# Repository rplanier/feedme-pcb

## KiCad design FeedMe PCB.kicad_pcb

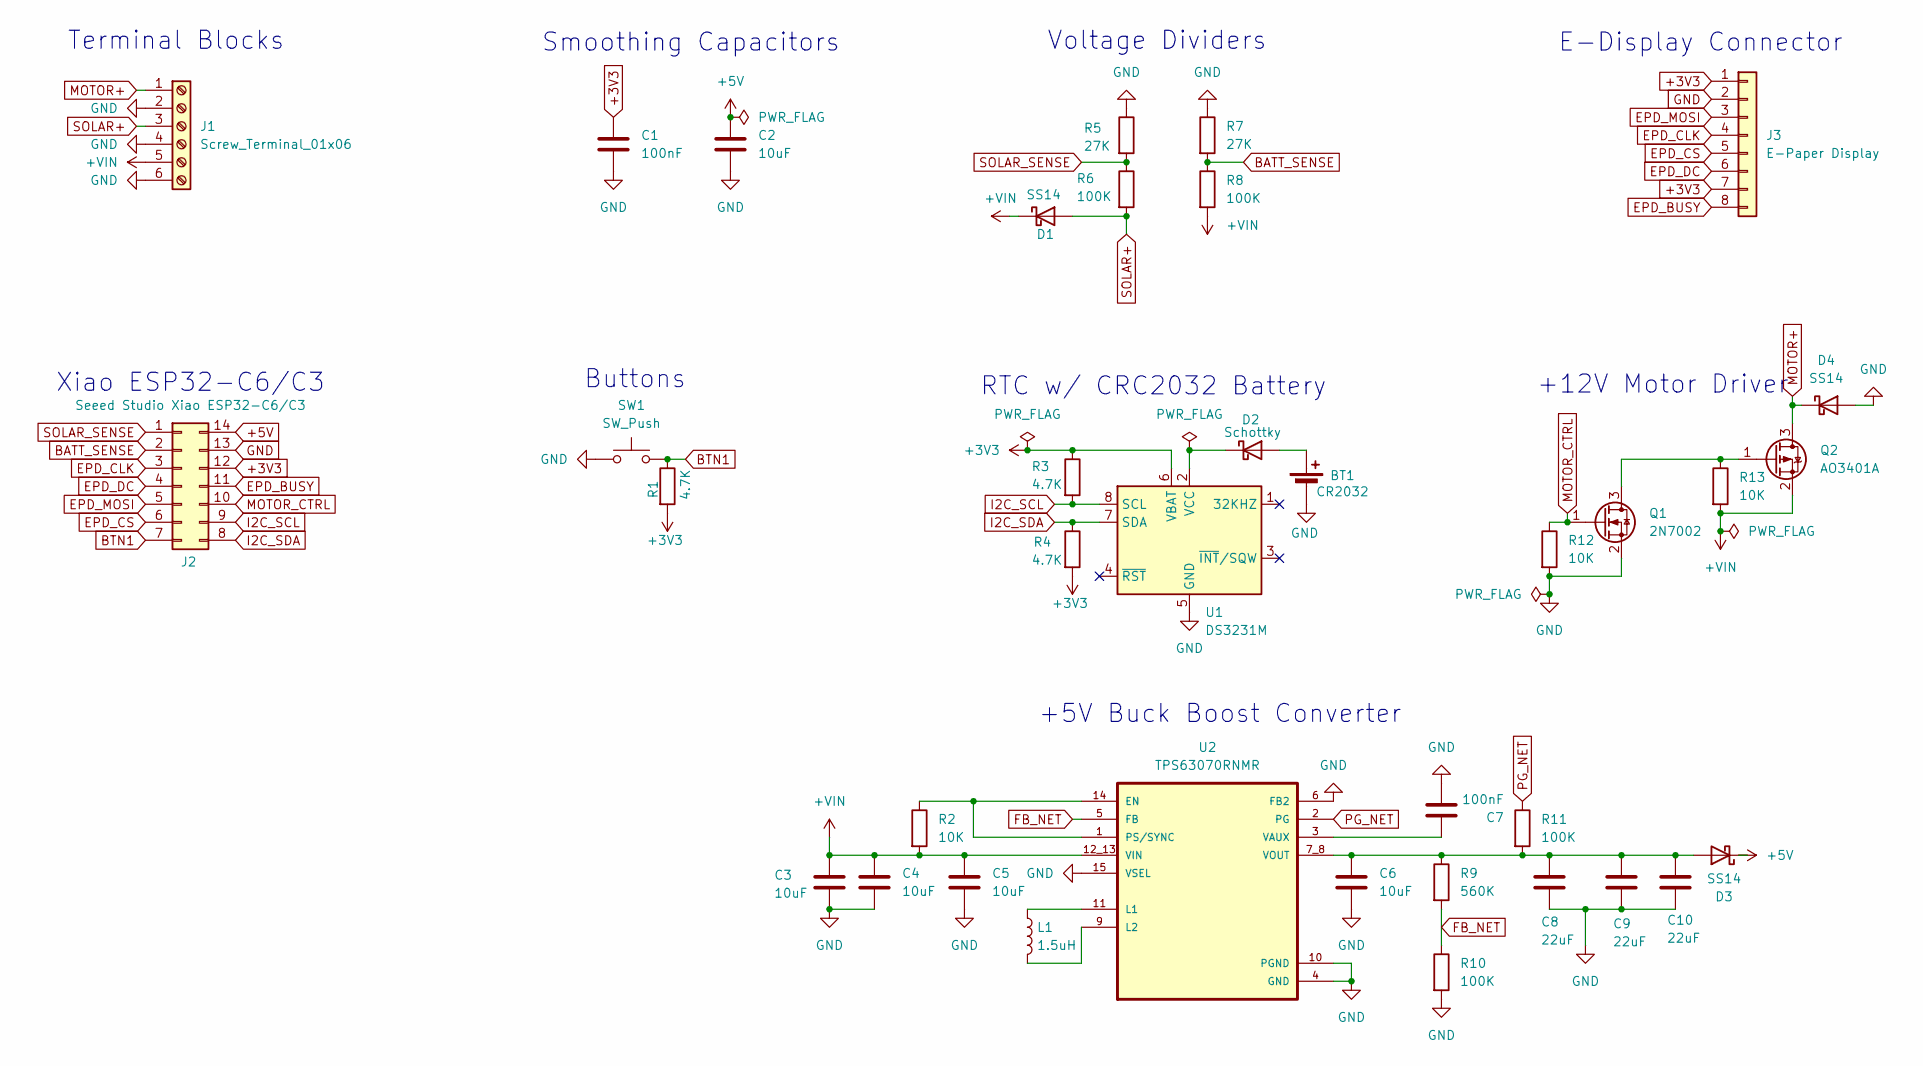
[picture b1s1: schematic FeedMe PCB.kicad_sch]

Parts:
BT1: CR2032; BatteryHolder_Keystone_3034_1x20mm
C1, C7: 100nF; C_0805_2012Metric_Pad1.18x1.45mm_HandSolder
C2: 10uF; C_0805_2012Metric_Pad1.18x1.45mm_HandSolder
C3, C4, C5, C6: 10uF; C_1206_3216Metric_Pad1.33x1.80mm_HandSolder
C8, C9, C10: 22uF; C_1206_3216Metric_Pad1.33x1.80mm_HandSolder
D1, D3, D4: SS14; D_SMA_Handsoldering
D2: Schottky; D_SOD-123
J1: Screw_Terminal_01x06; PhoenixContact_MSTBVA_2,5_6-G-5,08_1x06_P5.08mm_Vertical
J2: Seeed Studio Xiao ESP32-C6/C3; MCU_Seeed_Xiao_ESP32C6_Through_Hole
J3: E-Paper Display; JST_PH_S8B-PH-K_1x08_P2.00mm_Horizontal
L1: 1.5uH; L_Coilcraft_XAL4030-XXX
Q1: 2N7002; SOT-23
Q2: AO3401A; SOT-23
R1, R3, R4: 4.7K; R_0805_2012Metric_Pad1.20x1.40mm_HandSolder
R2, R12, R13: 10K; R_0805_2012Metric_Pad1.20x1.40mm_HandSolder
R5, R7: 27K; R_0805_2012Metric_Pad1.20x1.40mm_HandSolder
R6, R8, R10, R11: 100K; R_0805_2012Metric_Pad1.20x1.40mm_HandSolder
R9: 560K; R_0805_2012Metric_Pad1.20x1.40mm_HandSolder
SW1: SW_Push; SW_SPST_TL3342
U1: DS3231M; SOIC-8_3.9x4.9mm_P1.27mm
U2: TPS63070RNMR; VREG_TPS63070RNMR

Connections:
+3V3: C1.1, J2.12, J3.1, J3.7, R1.2, R3.1, R4.2, U1.6 (VBAT)
+5V: C2.1, D3.1 (K), J2.14
+VIN: C3.1, C4.1, C5.1, D1.1 (K), J1.5, Q2.2 (S), R2.2, R8.2, R13.2, U2.12_13 (VIN)
BATT_SENSE: J2.2, R7.2, R8.1
BTN1: J2.7, R1.1, SW1.2
EPD_BUSY: J2.11, J3.8
EPD_CLK: J2.3, J3.4
EPD_CS: J2.6, J3.5
EPD_DC: J2.4, J3.6
EPD_MOSI: J2.5, J3.3
FB_NET: R9.2, R10.1, U2.5 (FB)
GND: BT1.2 (-), C1.2, C2.2, C3.2, C4.2, C5.2, C6.2, C7.2, C8.2, C9.2, C10.2, D4.2 (A), J1.2, J1.4, J1.6, J2.13, J3.2, Q1.2 (S), R5.1, R7.1, R10.2, R12.2, SW1.1, U1.5 (GND), U2.4 (GND), U2.6 (FB2), U2.10 (PGND), U2.15 (VSEL)
I2C_SCL: J2.9, R3.2, U1.8 (SCL)
I2C_SDA: J2.8, R4.1, U1.7 (SDA)
MOTOR+: D4.1 (K), J1.1, Q2.3 (D)
MOTOR_CTRL: J2.10, Q1.1 (G), R12.1
unnamed: BT1.1 (+), D2.2 (A)
unnamed: D2.1 (K), U1.2 (VCC)
unnamed: C6.1, C8.1, C9.1, C10.1, D3.2 (A), R9.1, R11.2, U2.7_8 (VOUT)
unnamed: Q1.3 (D), Q2.1 (G), R13.1
unnamed: R2.1, U2.1 (PS/SYNC), U2.14 (EN)
unnamed: L1.1, U2.11 (L1)
unnamed: L1.2, U2.9 (L2)
unnamed: C7.1, U2.3 (VAUX)
PG_NET: R11.1, U2.2 (PG)
SOLAR+: D1.2 (A), J1.3, R6.2
SOLAR_SENSE: J2.1, R5.2, R6.1

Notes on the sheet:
E-Display Connector
Buttons
+5V Buck Boost Converter
Xiao ESP32-C6/C3
RTC w/ CRC2032 Battery
Voltage Dividers
+12V Motor Driver
Smoothing Capacitors
Terminal Blocks

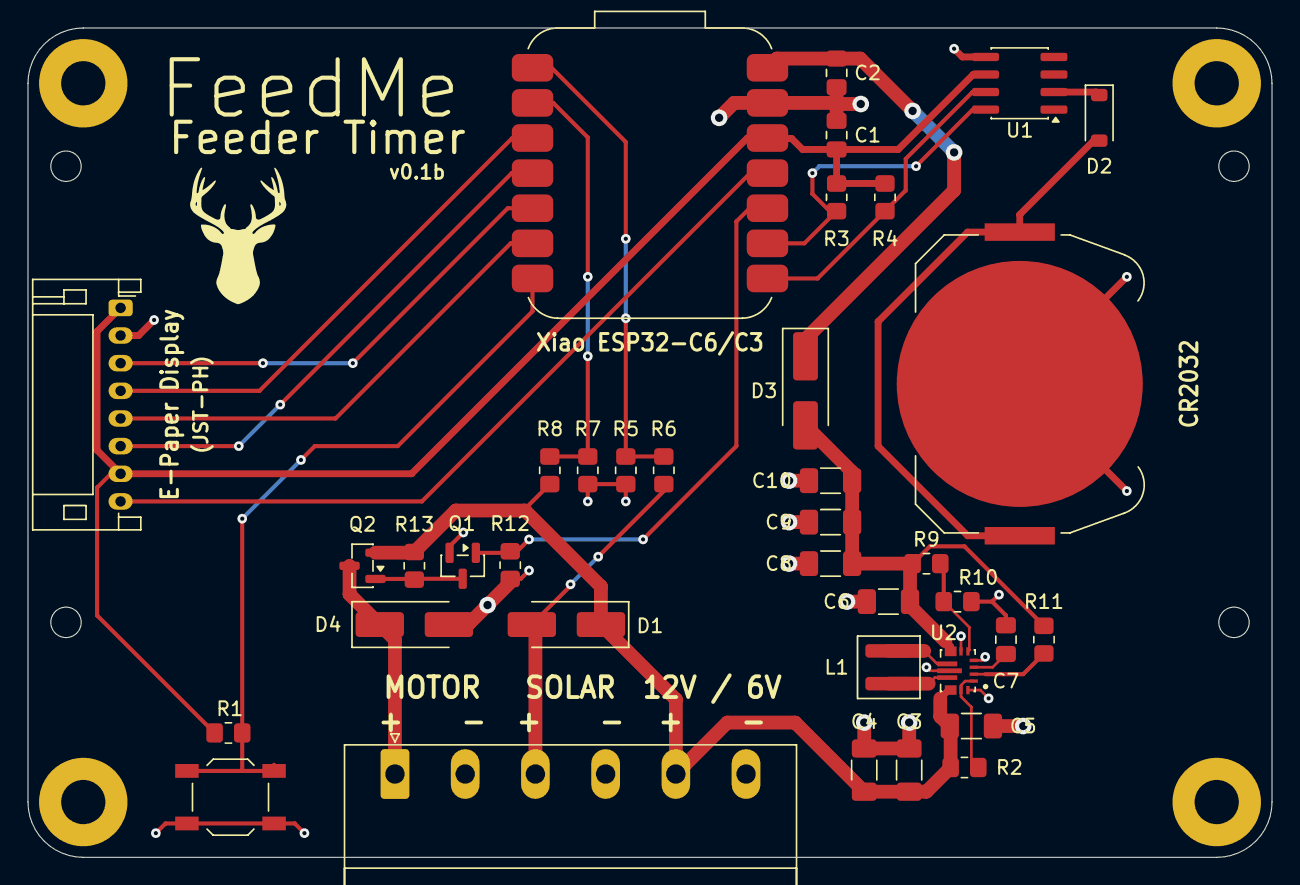
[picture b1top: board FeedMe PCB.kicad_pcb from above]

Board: 2 copper layers, 90.0 x 60.0 mm, 37 parts (0 on the bottom side), 27 nets.

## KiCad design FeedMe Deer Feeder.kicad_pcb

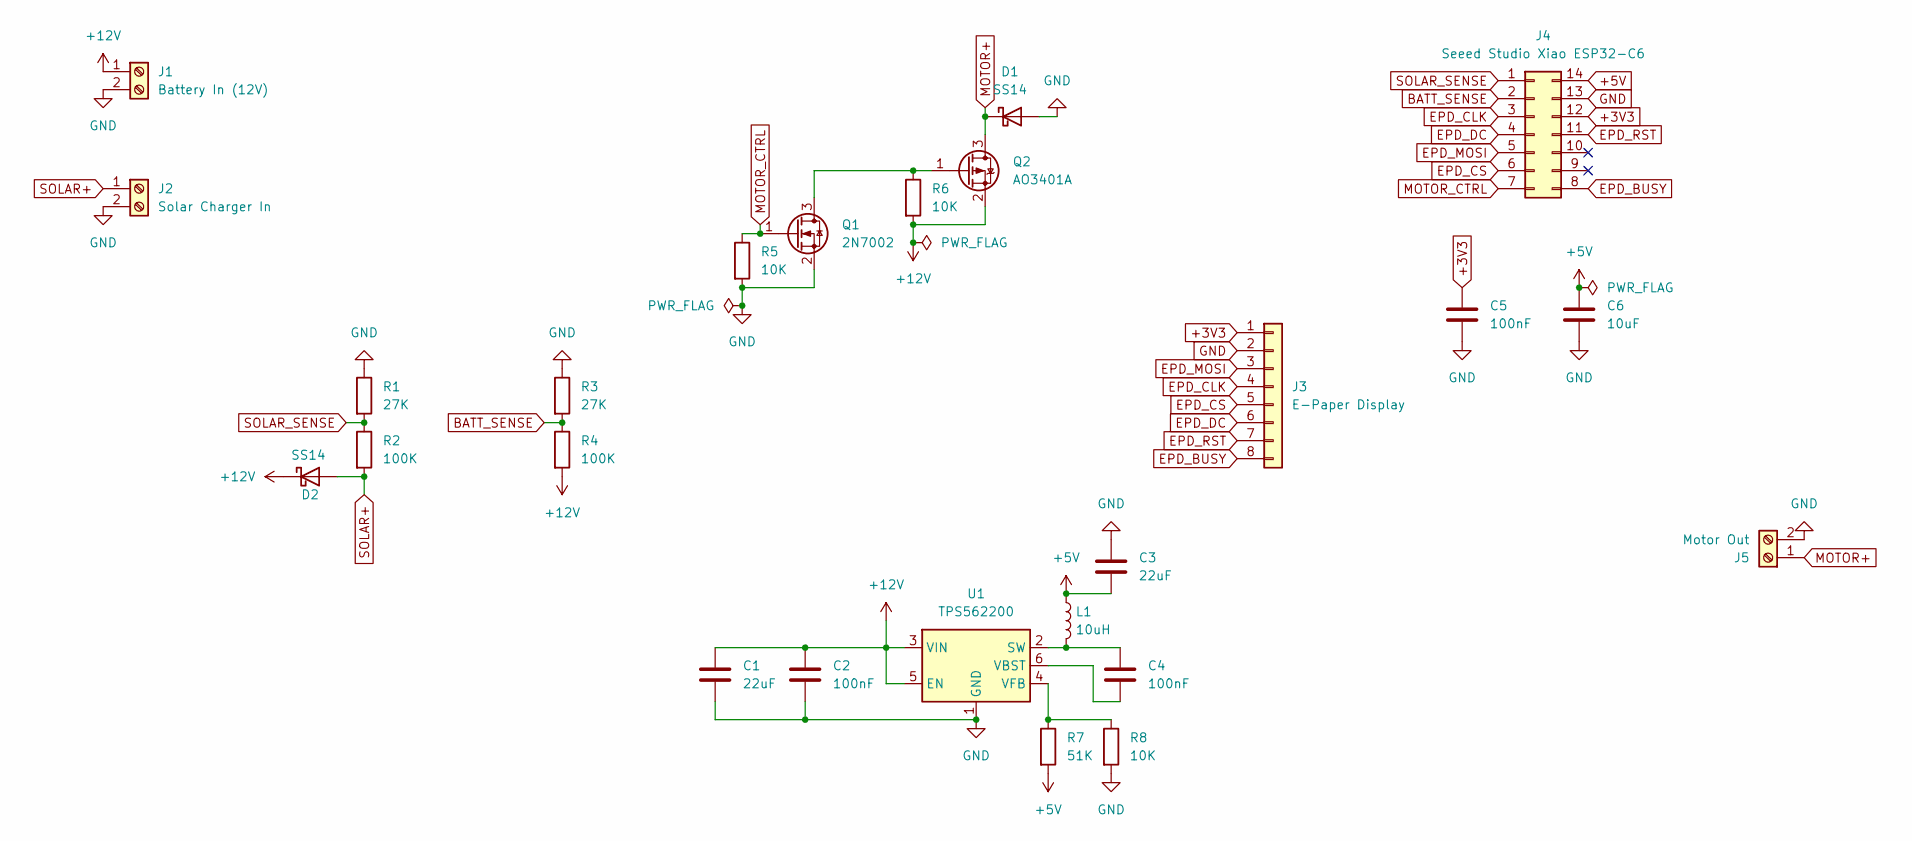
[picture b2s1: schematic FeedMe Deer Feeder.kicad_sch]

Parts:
C1, C3: 22uF; C_1206_3216Metric
C2, C4, C5: 100nF; C_0805_2012Metric
C6: 10uF; C_0805_2012Metric
D1, D2: SS14; D_SMA
J1: Battery In (12V); TerminalBlock_Phoenix_MKDS-1,5-2_1x02_P5.00mm_Horizontal
J2: Solar Charger In; TerminalBlock_Phoenix_MKDS-1,5-2_1x02_P5.00mm_Horizontal
J3: E-Paper Display; JST_PH_B8B-PH-K_1x08_P2.00mm_Vertical
J4: Seeed Studio Xiao ESP32-C6; MCU_Seeed_ESP32C3
J5: Motor Out; TerminalBlock_Phoenix_MKDS-1,5-2_1x02_P5.00mm_Horizontal
L1: 10uH; L_Bourns_SRN6045TA
Q1: 2N7002; SOT-23
Q2: AO3401A; SOT-23
R1, R3: 27K; R_0805_2012Metric
R2, R4: 100K; R_0805_2012Metric
R5, R6, R8: 10K; R_0805_2012Metric
R7: 51K; R_0805_2012Metric
U1: TPS562200; SOT-23-6

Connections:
+3V3: C5.1, J3.1, J4.12
+5V: C3.2, C6.1, J4.14, L1.1, R7.2
+12V: C1.1, C2.1, D2.1 (K), J1.1, Q2.2 (S), R4.2, R6.2, U1.3 (VIN), U1.5 (EN)
BATT_SENSE: J4.2, R3.2, R4.1
EPD_BUSY: J3.8, J4.8
EPD_CLK: J3.4, J4.3
EPD_CS: J3.5, J4.6
EPD_DC: J3.6, J4.4
EPD_MOSI: J3.3, J4.5
EPD_RST: J3.7, J4.11
GND: C1.2, C2.2, C3.1, C5.2, C6.2, D1.2 (A), J1.2, J2.2, J3.2, J4.13, J5.2, Q1.2 (S), R1.1, R3.1, R5.2, R8.2, U1.1 (GND)
MOTOR+: D1.1 (K), J5.1, Q2.3 (D)
MOTOR_CTRL: J4.7, Q1.1 (G), R5.1
unnamed: Q1.3 (D), Q2.1 (G), R6.1
unnamed: C4.1, L1.2, U1.2 (SW)
unnamed: C4.2, U1.6 (VBST)
unnamed: R7.1, R8.1, U1.4 (VFB)
SOLAR+: D2.2 (A), J2.1, R2.2
SOLAR_SENSE: J4.1, R1.2, R2.1

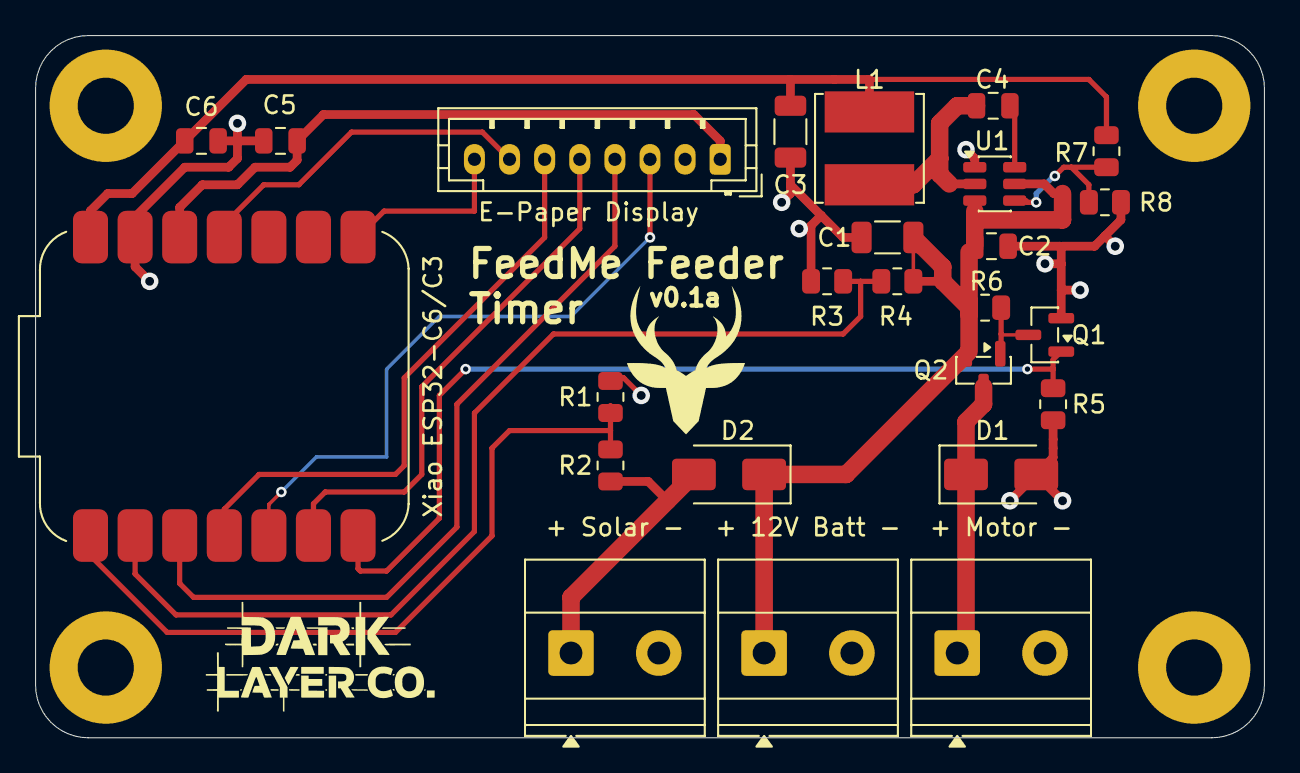
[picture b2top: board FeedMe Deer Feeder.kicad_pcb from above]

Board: 2 copper layers, 70.0 x 40.0 mm, 25 parts (0 on the bottom side), 19 nets.

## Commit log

2026-01-03 Initial commit - FeedMe PCB v0.1a
    Hardware design for FeedMe deer feeder timer replacement.
    Features:
    - XIAO ESP32-C6 (castellated mounting)
    - TPS562200 buck converter (12V to 5V)
    - P-channel high-side motor driver (AO3401A + 2N7002)
    - Battery voltage sensing (100K/27K divider)
2026-01-03 Rename project files to 'FeedMe PCB'
2026-01-30 v0.1b - Buck-boost converter, pluggable terminals, reliability fixes
